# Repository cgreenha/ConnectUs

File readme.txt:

This repository is meant for the senior design team "ConnectUs" at Valparaiso University.

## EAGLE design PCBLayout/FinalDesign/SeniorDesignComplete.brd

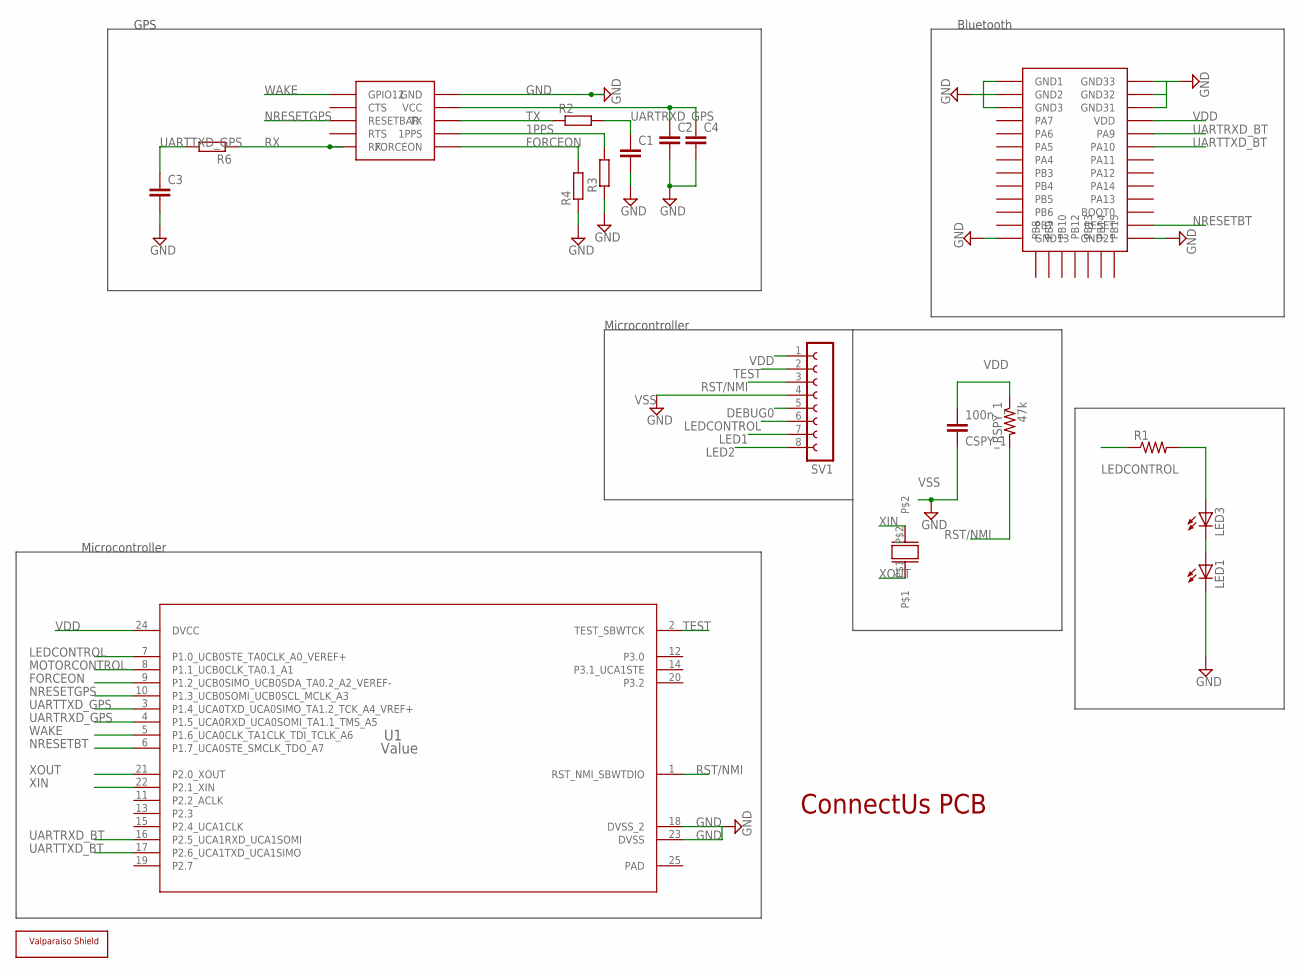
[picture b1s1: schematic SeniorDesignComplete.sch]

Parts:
C1, C2, C3, C4: C; C0805
CSPY_1: 100n; C1206
GPS(ORG1510): ORG1510
LED1, LED3: LED_ELD260; LED_LD260
R1: R-US_0204/2V; 0204V
R2, R3, R4, R6: R; R0805
RSPY_1: 47k; R1206
SV1: FE08-1; FE08
U1: Value; RGE0024G
U$2: BT121
U$11: VALPARAISO-SHIELD; VUSHIELD-200MIL
UCRY_1: ECX31-BSOLDERABLE; ECX31-B_EXPAND

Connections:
1PPS: GPS(ORG1510).1PPS, R3.2
DEBUG0: SV1.5
FORCEON: GPS(ORG1510).FORCEON, R4.2, U1.9 (P1.2_UCB0SIMO_UCB0SDA_TA0.2_A2_VEREF-)
GND: C1.2, C2.2, C3.2, C4.2, GPS(ORG1510).GND, LED1.K (C), R3.1, R4.1, U1.18 (DVSS_2), U1.23 (DVSS), U$2.GND1, U$2.GND2, U$2.GND3, U$2.GND13, U$2.GND21, U$2.GND31, U$2.GND32, U$2.GND33
LED1: SV1.7
LED2: SV1.8
LEDCONTROL: R1.1, SV1.6, U1.7 (P1.0_UCB0STE_TA0CLK_A0_VEREF+)
MOTORCONTROL: U1.8 (P1.1_UCB0CLK_TA0.1_A1)
unnamed: LED1.A, LED3.K (C)
unnamed: C2.1, C4.1, GPS(ORG1510).VCC
unnamed: LED3.A, R1.2
NRESETBT: U1.6 (P1.7_UCA0STE_SMCLK_TDO_A7), U$2.RESET
NRESETGPS: GPS(ORG1510).RESETBAR, U1.10 (P1.3_UCB0SOMI_UCB0SCL_MCLK_A3)
PAD: U1.25 (PAD)
RST/NMI: RSPY_1.2, SV1.3, U1.1 (RST_NMI_SBWTDIO)
RX: GPS(ORG1510).RX, R6.1
TEST: SV1.2, U1.2 (TEST_SBWTCK)
TX: GPS(ORG1510).TX, R2.1
UARTRXD_BT: U1.16 (P2.5_UCA1RXD_UCA1SOMI), U$2.PA9
UARTRXD_GPS: C1.1, R2.2, U1.4 (P1.5_UCA0RXD_UCA0SOMI_TA1.1_TMS_A5)
UARTTXD_BT: U1.17 (P2.6_UCA1TXD_UCA1SIMO), U$2.PA10
UARTTXD_GPS: C3.1, R6.2, U1.3 (P1.4_UCA0TXD_UCA0SIMO_TA1.2_TCK_A4_VREF+)
VDD: CSPY_1.2, RSPY_1.1, SV1.1, U1.24 (DVCC), U$2.VDD
VSS: CSPY_1.1, SV1.4
WAKE: GPS(ORG1510).GPIO12, U1.5 (P1.6_UCA0CLK_TA1CLK_TDI_TCLK_A6)
XIN: U1.22 (P2.1_XIN), UCRY_1.P$2
XOUT: U1.21 (P2.0_XOUT), UCRY_1.P$1

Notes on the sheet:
ConnectUs PCB
Bluetooth
GPS
Microcontroller

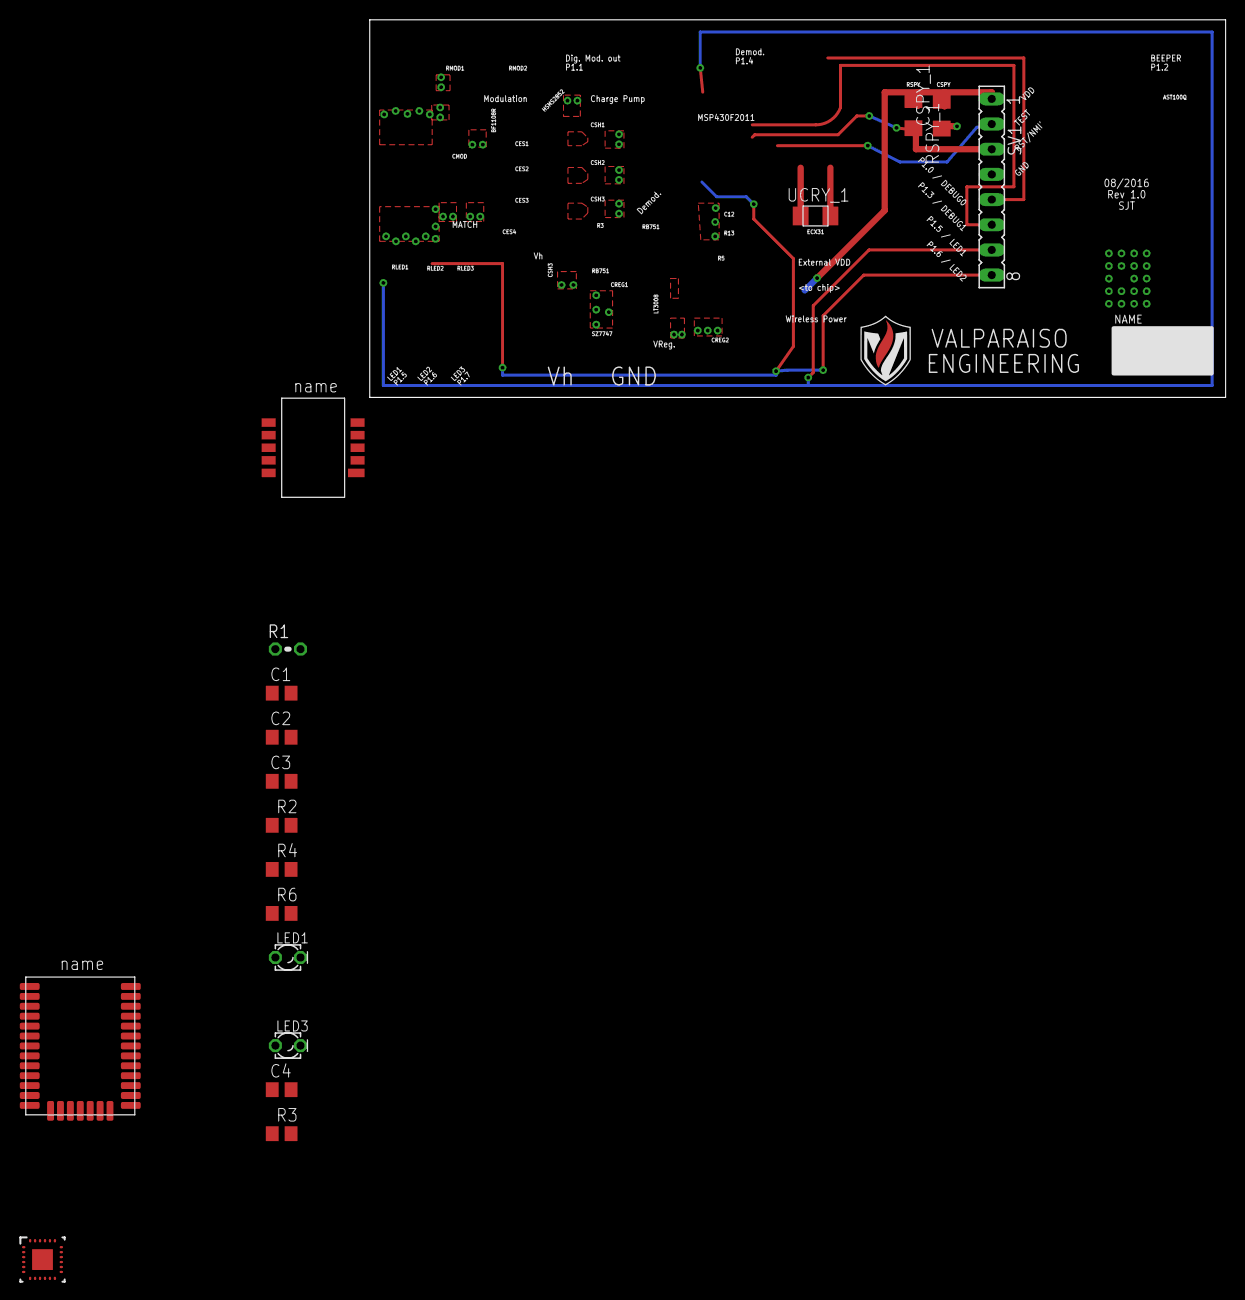
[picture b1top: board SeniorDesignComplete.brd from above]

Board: 2 copper layers, 86.4 x 38.1 mm, 19 parts (0 on the bottom side), 22 nets.

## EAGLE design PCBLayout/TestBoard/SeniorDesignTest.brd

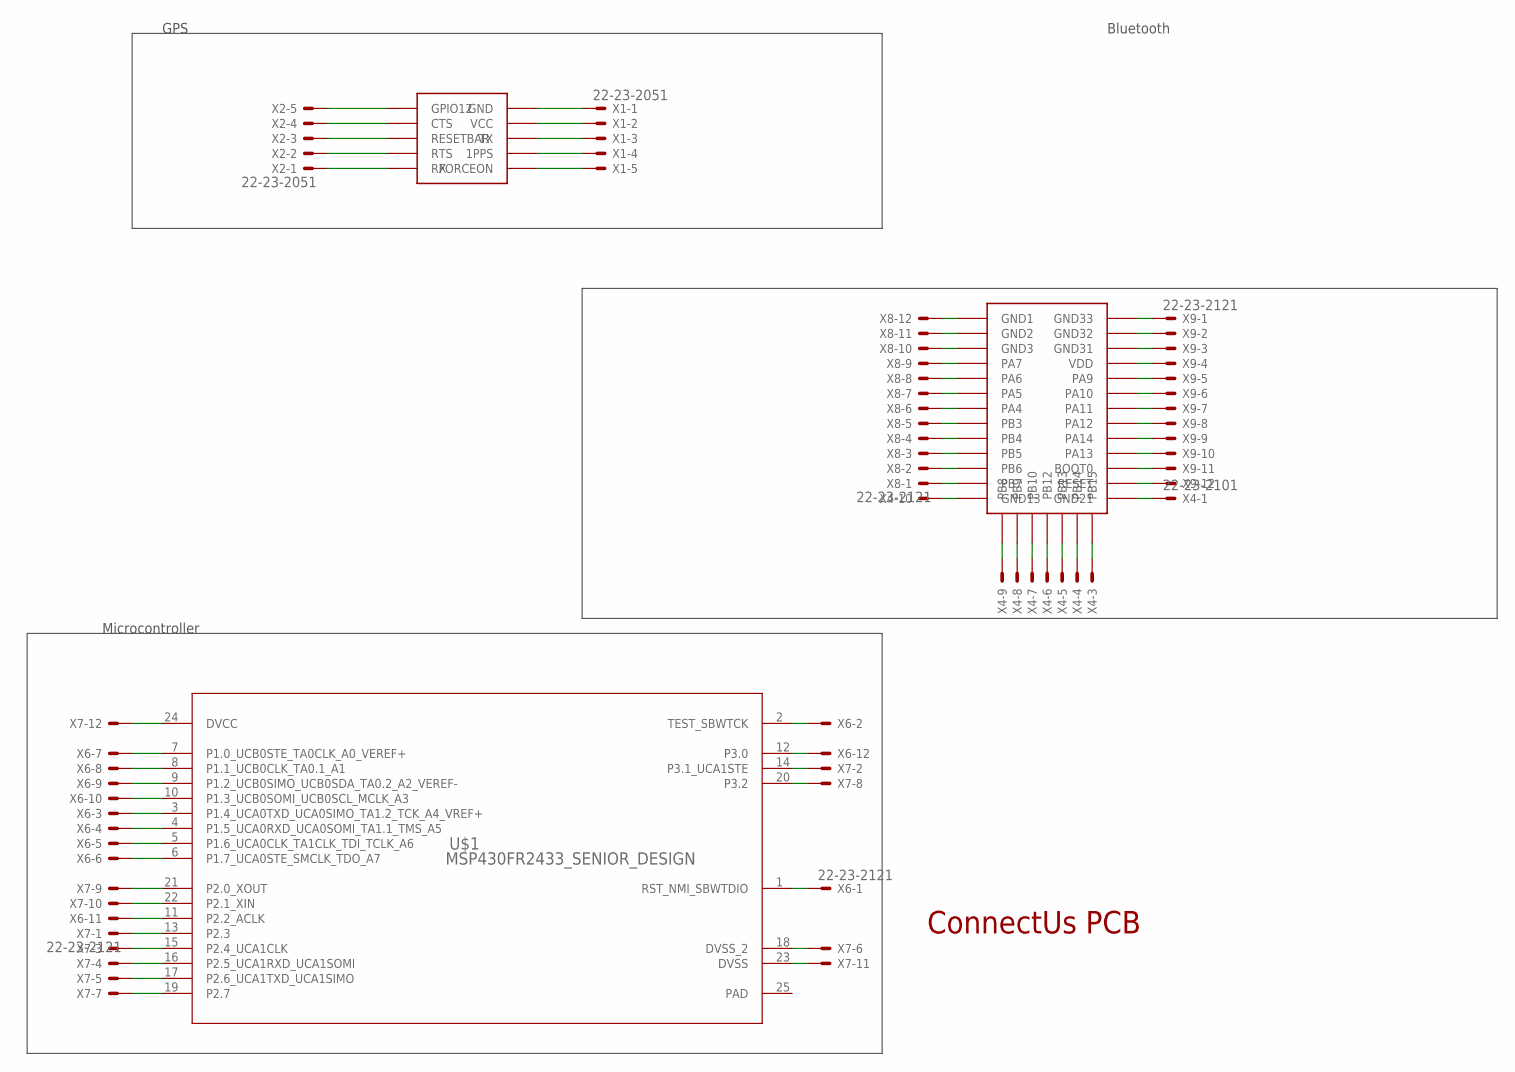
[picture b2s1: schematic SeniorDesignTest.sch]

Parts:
GPS(ORG1510): ORG1510
U$1: MSP430FR2433_SENIOR_DESIGN; RGE0024G_NV
U$2: BT121
X1, X2: 22-23-2051
X4: 22-23-2101
X6, X7, X8, X9: 22-23-2121

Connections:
unnamed: U$1.24 (DVCC), X7.12
unnamed: U$1.7 (P1.0_UCB0STE_TA0CLK_A0_VEREF+), X6.7
unnamed: U$1.8 (P1.1_UCB0CLK_TA0.1_A1), X6.8
unnamed: U$1.9 (P1.2_UCB0SIMO_UCB0SDA_TA0.2_A2_VEREF-), X6.9
unnamed: U$2.PB3, X8.5
unnamed: U$1.10 (P1.3_UCB0SOMI_UCB0SCL_MCLK_A3), X6.10
unnamed: U$1.3 (P1.4_UCA0TXD_UCA0SIMO_TA1.2_TCK_A4_VREF+), X6.3
unnamed: U$1.4 (P1.5_UCA0RXD_UCA0SOMI_TA1.1_TMS_A5), X6.4
unnamed: U$1.5 (P1.6_UCA0CLK_TA1CLK_TDI_TCLK_A6), X6.5
unnamed: U$1.6 (P1.7_UCA0STE_SMCLK_TDO_A7), X6.6
unnamed: U$2.PB4, X8.4
unnamed: U$1.21 (P2.0_XOUT), X7.9
unnamed: U$1.22 (P2.1_XIN), X7.10
unnamed: U$1.11 (P2.2_ACLK), X6.11
unnamed: U$1.13 (P2.3), X7.1
unnamed: U$2.PB5, X8.3
unnamed: U$1.15 (P2.4_UCA1CLK), X7.3
unnamed: U$1.16 (P2.5_UCA1RXD_UCA1SOMI), X7.4
unnamed: U$1.17 (P2.6_UCA1TXD_UCA1SIMO), X7.5
unnamed: U$1.19 (P2.7), X7.7
unnamed: U$1.2 (TEST_SBWTCK), X6.2
unnamed: U$1.12 (P3.0), X6.12
unnamed: U$1.14 (P3.1_UCA1STE), X7.2
unnamed: U$1.20 (P3.2), X7.8
unnamed: U$1.1 (RST_NMI_SBWTDIO), X6.1
unnamed: U$1.18 (DVSS_2), X7.6
unnamed: U$1.23 (DVSS), X7.11
unnamed: U$2.GND1, X8.12
unnamed: U$2.GND2, X8.11
unnamed: U$2.GND3, X8.10
unnamed: U$2.PA7, X8.9
unnamed: U$2.PA6, X8.8
unnamed: U$2.PA5, X8.7
unnamed: U$2.PA4, X8.6
unnamed: U$2.PB6, X8.2
unnamed: U$2.PB7, X8.1
unnamed: U$2.GND13, X4.10
unnamed: U$2.PA12, X9.8
unnamed: U$2.PA14, X9.9
unnamed: U$2.PA13, X9.10
unnamed: U$2.GND33, X9.1
unnamed: U$2.GND32, X9.2
unnamed: U$2.GND31, X9.3
unnamed: U$2.VDD, X9.4
unnamed: U$2.PA9, X9.5
unnamed: U$2.PA10, X9.6
unnamed: U$2.PA11, X9.7
unnamed: U$2.BOOT0, X9.11
unnamed: U$2.RESET, X9.12
unnamed: U$2.GND21, X4.1
unnamed: U$2.PB8, X4.9
unnamed: U$2.PB9, X4.8
unnamed: U$2.PB10, X4.7
unnamed: U$2.PB12, X4.6
unnamed: U$2.PB13, X4.5
unnamed: U$2.PB14, X4.4
unnamed: U$2.PB15, X4.3
unnamed: GPS(ORG1510).GPIO12, X2.5
unnamed: GPS(ORG1510).CTS, X2.4
unnamed: GPS(ORG1510).RESETBAR, X2.3
unnamed: GPS(ORG1510).RTS, X2.2
unnamed: GPS(ORG1510).GND, X1.1
unnamed: GPS(ORG1510).VCC, X1.2
unnamed: GPS(ORG1510).TX, X1.3
unnamed: GPS(ORG1510).1PPS, X1.4
unnamed: GPS(ORG1510).FORCEON, X1.5
PAD: U$1.25 (PAD)
RX: GPS(ORG1510).RX, X2.1

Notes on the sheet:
ConnectUs PCB
Bluetooth
GPS
Microcontroller

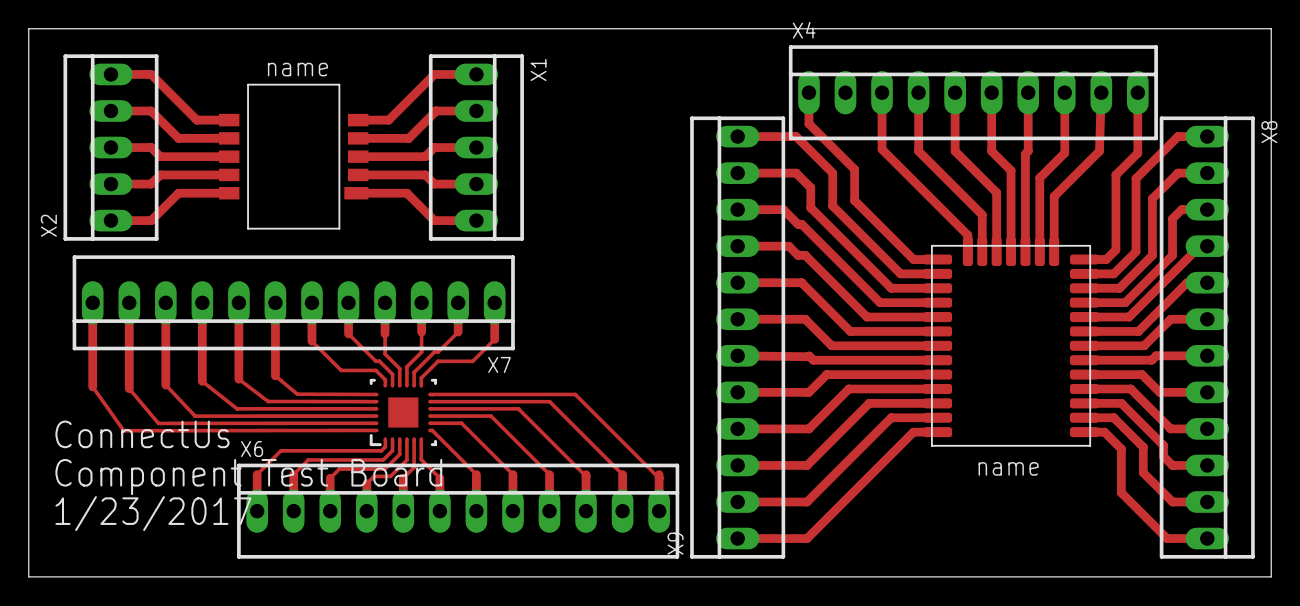
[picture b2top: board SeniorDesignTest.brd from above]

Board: 2 copper layers, 86.4 x 38.1 mm, 10 parts (0 on the bottom side), 67 nets.

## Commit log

2017-01-19 Testing remote commit
2017-01-28 Added working LED APP
2017-01-29 Added bluetooth microcontroller code
2017-01-29 Added sleep button code for microcontroller
2017-01-29 Add files via upload
    LED app for Milestone 1
2017-01-29 Adding 3 LED test code for microcontroller and App
2017-01-31 NeoPixel Microcontroller Code Added
2017-02-07 i just added ada on the txt file
2017-02-11 PCB Designs Added
2017-03-19 Added Code for Small MSP (MSP430FR4233)
2017-03-23 Added code to working MSP430FR2433 code with Bluetooth and GPS
2017-04-02 Create msp430fr2433_rgb
2017-04-02 Rename main.c to msp430fr2433.c
2017-04-04 PCB Designs and MSP430 code updates
2017-04-18 Adding versions 4 and 5 for code
2017-04-22 The final working software version (v11) for the PCB has been added.
2017-05-02 Updated mobile applicaiton and MSP430 code for push button.
2017-05-02 MSP430 code with push button
2017-05-06 Final version of PCB, V13
